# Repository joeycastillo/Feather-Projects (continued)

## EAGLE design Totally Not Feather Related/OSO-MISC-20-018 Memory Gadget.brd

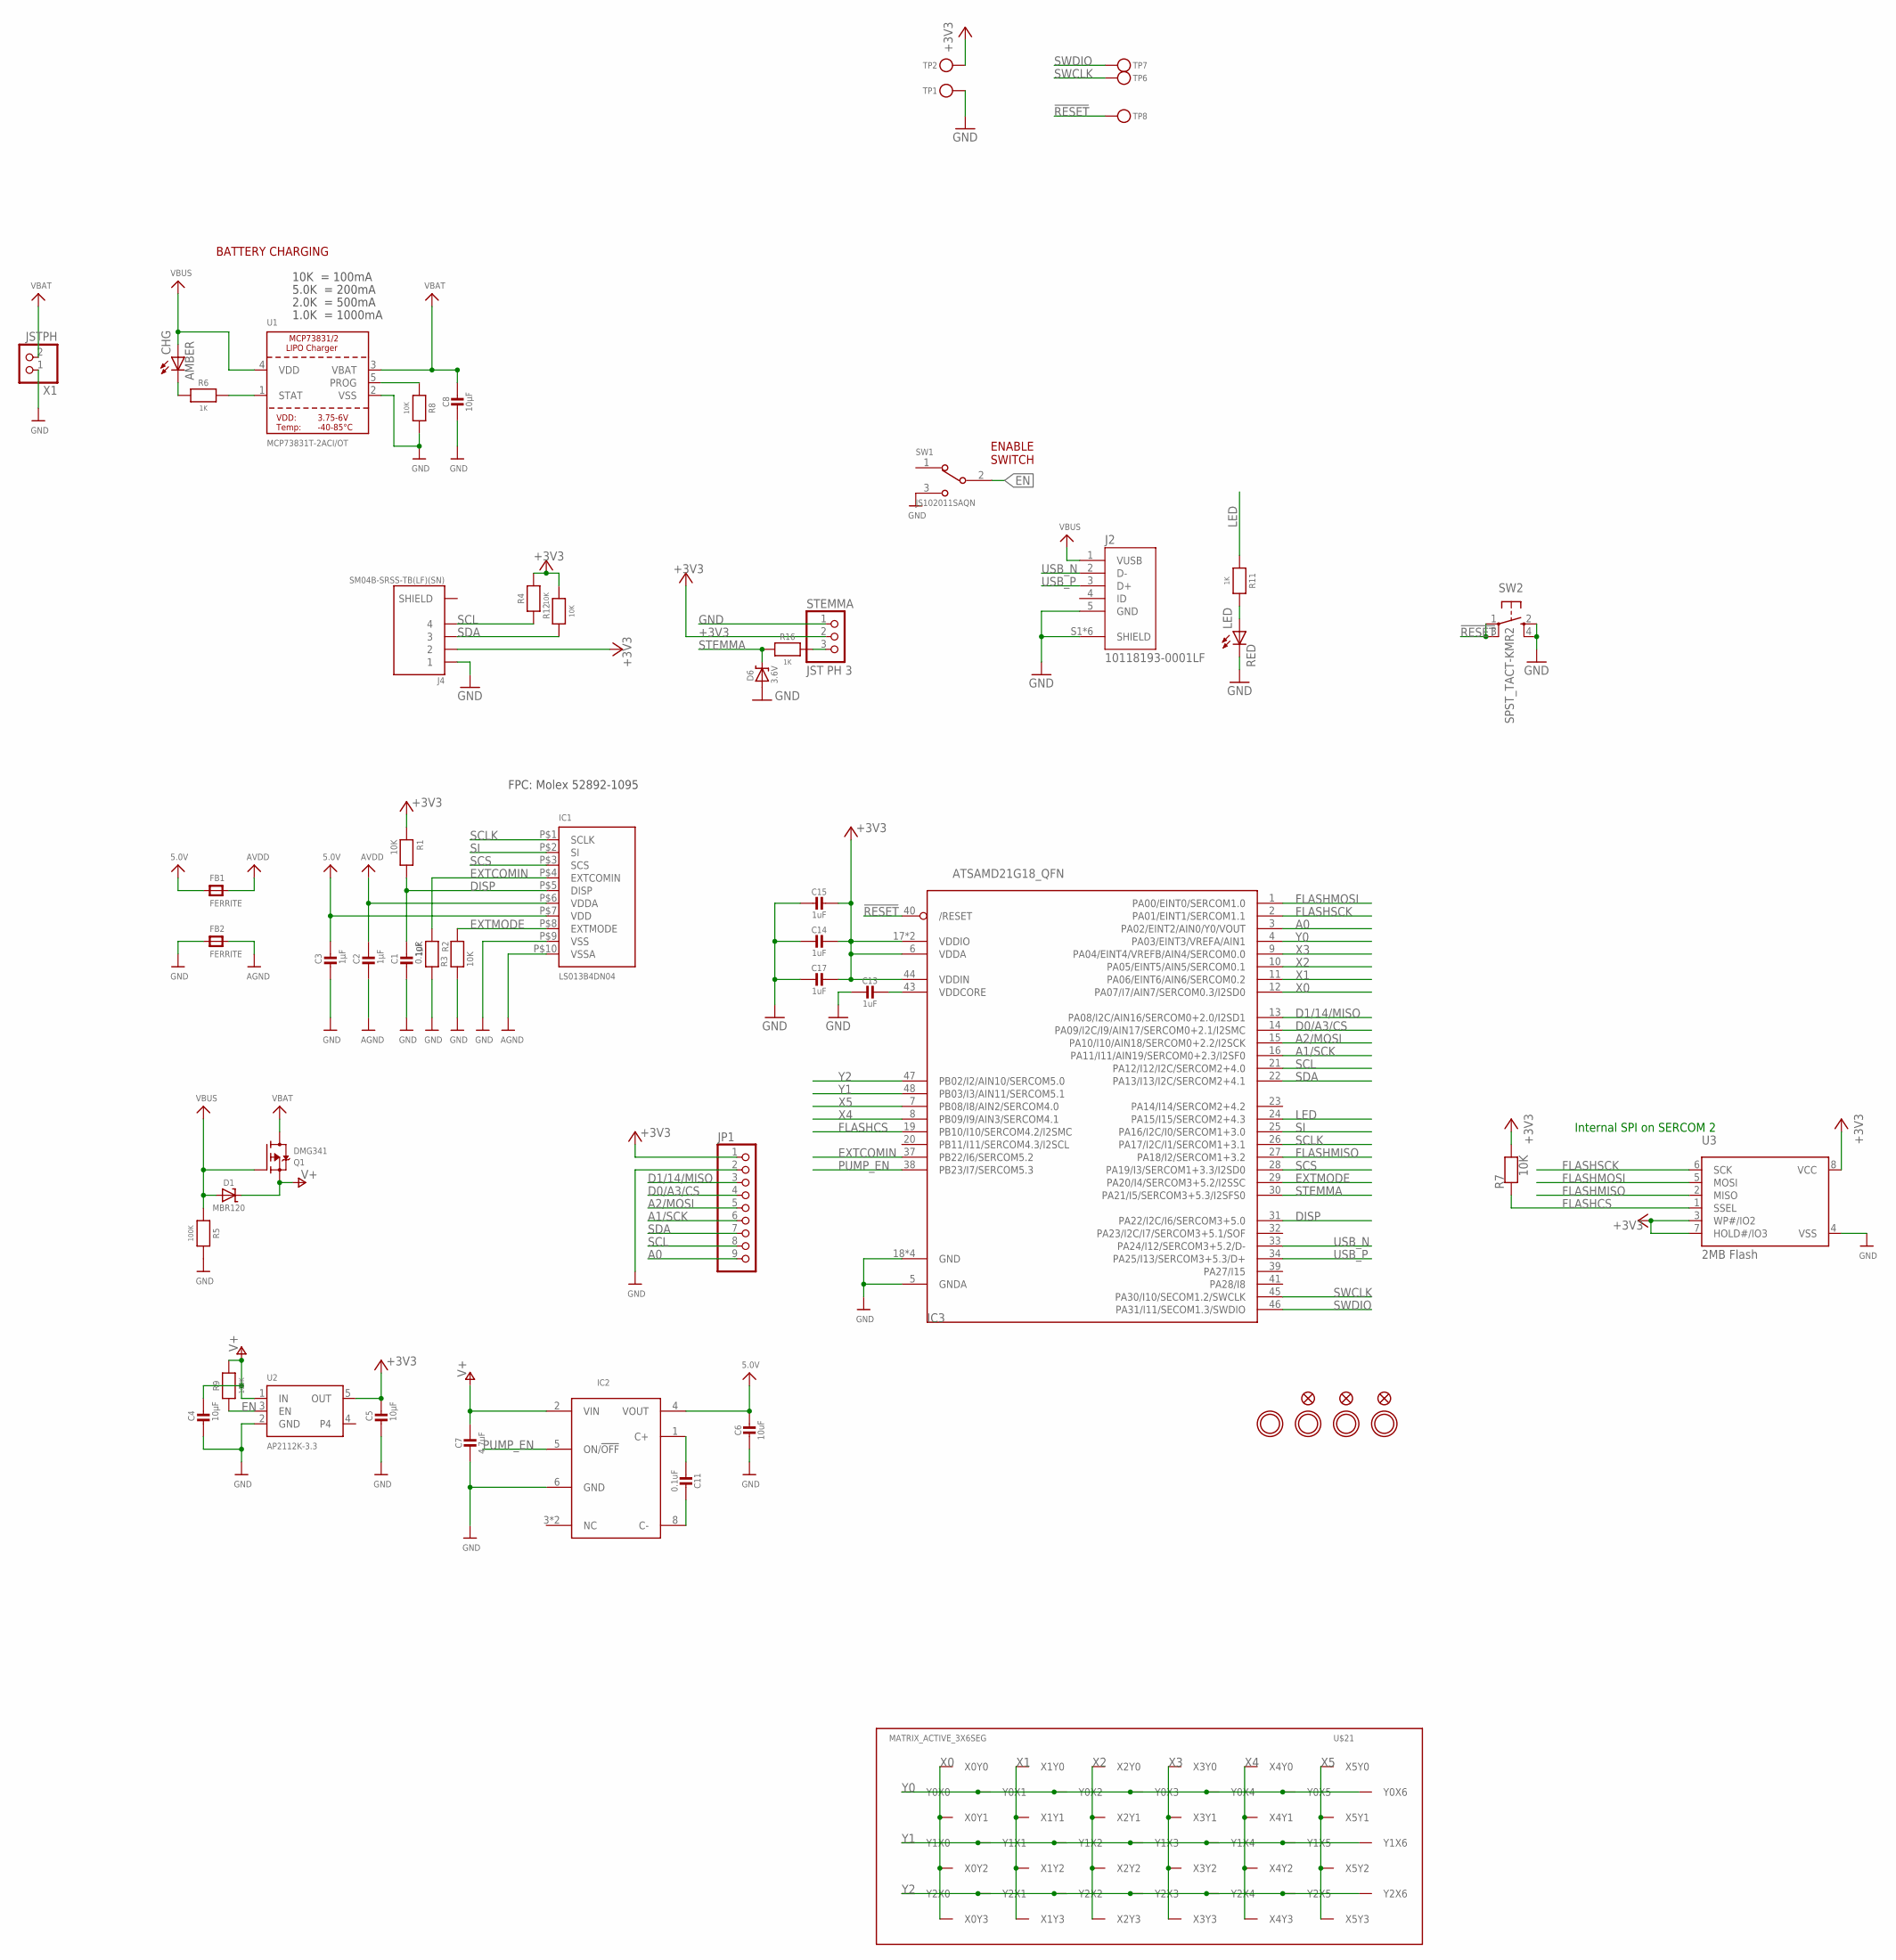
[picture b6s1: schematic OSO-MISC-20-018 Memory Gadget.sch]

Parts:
C1: 0.1µF; 0603-NO
C2: 1µF; 0805_10MGAP
C3: 1µF; 0805-NO
C4, C5, C8: 10µF; 0805-NO
C6: 10uF; 0805-NO
C7: 4.7uF; 0805-NO
C11: 0.1uF; 0805-NO
C13, C14, C15, C17: 1uF; 0603-NO
CHG: AMBER; CHIP-LED0805
D1: MBR120; SOD-123
D6: 3.6V; SOD-123
FB1, FB2: FERRITE; _0805
FID1, FID2, FID3: FIDUCIAL_1MM
IC1: LS013B4DN04; SHARP_2.7IN
IC2: S-882150APH; SNT-8A
IC3: ATSAMD21G18_QFN; TQFN48_7MM
J2: 10118193-0001LF; FCI_10118193-0001LF
J4: SM04B-SRSS-TB(LF)(SN); JST_SM04B-SRSS-TB(LF)(SN)
JP1: HEADER-1X9_JSTSH; JST_SH9
LED: RED; CHIP-LED0805
Q1: DMG341; SOT23-R
R1, R2, R3, R4, R7, R12: 10K; 0603-NO
R5, R9: 100K; 0805-NO
R6, R11: 1K; 0805-NO
R8: 10K; 0805-NO
R16: 1K; _0805MP
STEMMA: JST PH 3; JSTPH3
SW1: JS102011SAQN; SW_JS102011SAQN
SW2: SPST_TACT-KMR2; KMR2
TP1, TP2, TP6, TP7, TP8: TESTPOINTROUND2MMNO; TESTPOINT_ROUND_2MM_NO
U1: MCP73831T-2ACI/OT; SOT23-5
U2: AP2112K-3.3; SOT23-5
U3: 2MB Flash; SOIC8_150MIL
U$9, U$10, U$27, U$28: MOUNTINGHOLE2.5; MOUNTINGHOLE_2.5_PLATED
U$21: MATRIX_ACTIVE_3X6SEG; MATRIX_ACTIVE_3X6SEG_6MM
X1: JSTPH; JSTPH2

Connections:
5.0V: C3.1, C6.1, FB1.1, IC1.P$7 (VDD), IC2.4 (VOUT)
!RESET: IC3.40 (/RESET), SW2.1, SW2.3 (P1), TP8.P$1
+3V3: C5.1, C14.1, C15.1, C17.1, IC3.6 (VDDA), IC3.17 (VDDIO), IC3.36 (VDDIO), IC3.44 (VDDIN), J4.2, JP1.1, R1.1, R4.2, R7.2, R12.2, STEMMA.2, TP2.P$1, U2.5 (OUT), U3.3 (WP#/IO2), U3.7 (HOLD#/IO3), U3.8 (VCC)
A0: IC3.3 (PA02/EINT2/AIN0/Y0/VOUT), JP1.9
A1/SCK: IC3.16 (PA11/I11/AIN19/SERCOM0+2.3/I2SF0), JP1.6
A2/MOSI: IC3.15 (PA10/I10/AIN18/SERCOM0+2.2/I2SCK), JP1.5
AGND: C2.2, FB2.2, IC1.P$10 (VSSA)
AVDD: C2.1, FB1.2, IC1.P$6 (VDDA)
D0/A3/CS: IC3.14 (PA09/I2C/I9/AIN17/SERCOM0+2.1/I2SMC), JP1.4
D1/14/MISO: IC3.13 (PA08/I2C/AIN16/SERCOM0+2.0/I2SD1), JP1.3
DISP: C1.1, IC1.P$5 (DISP), IC3.31 (PA22/I2C/I6/SERCOM3+5.0), R1.2
EN: R9.1, SW1.2, U2.3 (EN)
EXTCOMIN: IC1.P$4 (EXTCOMIN), IC3.37 (PB22/I6/SERCOM5.2), R2.1
EXTMODE: IC1.P$8 (EXTMODE), IC3.29 (PA20/I4/SERCOM3+5.2/I2SSC), R3.2
FLASHCS: IC3.19 (PB10/I10/SERCOM4.2/I2SMC), R7.1, U3.1 (SSEL)
FLASHMISO: IC3.27 (PA18/I2/SERCOM1+3.2), U3.2 (MISO)
FLASHMOSI: IC3.1 (PA00/EINT0/SERCOM1.0), U3.5 (MOSI)
FLASHSCK: IC3.2 (PA01/EINT1/SERCOM1.1), U3.6 (SCK)
GND: C1.2, C3.2, C4.2, C5.2, C6.2, C7.2, C8.2, C13.2, C14.2, C15.2, C17.2, D6.A, FB2.1, IC1.P$9 (VSS), IC2.6 (GND), IC3.5 (GNDA), IC3.18 (GND), IC3.35 (GND), IC3.42 (GND), IC3.THERMAL (GND), J2.5 (GND), J2.S1 (SHIELD), J2.S2 (SHIELD), J2.S3 (SHIELD), J2.S4 (SHIELD), J2.S5 (SHIELD), J2.S6 (SHIELD), J4.1, JP1.2, LED.C, R2.2, R3.1, R5.2, R8.2, STEMMA.1, SW1.3, SW2.2 (S), SW2.4 (S1), TP1.P$1, U1.2 (VSS), U2.2 (GND), U3.4 (VSS), X1.1
LED: IC3.24 (PA15/I15/SERCOM2+4.3), R11.1
unnamed: LED.A, R11.2
unnamed: CHG.C, R6.1
unnamed: C11.2, IC2.1 (C+)
unnamed: C11.1, IC2.8 (C-)
PROG: R8.1, U1.5 (PROG)
PUMP_EN: IC2.5 (ON/!OFF), IC3.38 (PB23/I7/SERCOM5.3)
SCL: IC3.21 (PA12/I12/I2C/SERCOM2+4.0), J4.4, JP1.8, R4.1
SCLK: IC1.P$1 (SCLK), IC3.26 (PA17/I2C/I1/SERCOM1+3.1)
SCS: IC1.P$3 (SCS), IC3.28 (PA19/I3/SERCOM1+3.3/I2SD0)
SDA: IC3.22 (PA13/I13/I2C/SERCOM2+4.1), J4.3, JP1.7, R12.1
SI: IC1.P$2 (SI), IC3.25 (PA16/I2C/I0/SERCOM1+3.0)
STAT: R6.2, U1.1 (STAT)
STEMMA: D6.C, IC3.30 (PA21/I5/SERCOM3+5.3/I2SFS0), R16.2
STEMMA_: R16.1, STEMMA.3
SWCLK: IC3.45 (PA30/I10/SECOM1.2/SWCLK), TP6.P$1
SWDIO: IC3.46 (PA31/I11/SECOM1.3/SWDIO), TP7.P$1
USB_N: IC3.33 (PA24/I12/SERCOM3+5.2/D-), J2.2 (D-)
USB_P: IC3.34 (PA25/I13/SERCOM3+5.3/D+), J2.3 (D+)
V+: C4.1, C7.1, D1.C, IC2.2 (VIN), Q1.2 (S), R9.2, U2.1 (IN)
VBAT: C8.1, Q1.3 (D), U1.3 (VBAT), X1.2
VBUS: CHG.A, D1.A, J2.1 (VUSB), Q1.1 (G), R5.1, U1.4 (VDD)
VDDCORE: C13.1, IC3.43 (VDDCORE)
X0: IC3.12 (PA07/I7/AIN7/SERCOM0.3/I2SD0), U$21.X0Y0, U$21.X0Y1, U$21.X0Y2, U$21.X0Y3
X1: IC3.11 (PA06/EINT6/AIN6/SERCOM0.2), U$21.X1Y0, U$21.X1Y1, U$21.X1Y2, U$21.X1Y3
X2: IC3.10 (PA05/EINT5/AIN5/SERCOM0.1), U$21.X2Y0, U$21.X2Y1, U$21.X2Y2, U$21.X2Y3
X3: IC3.9 (PA04/EINT4/VREFB/AIN4/SERCOM0.0), U$21.X3Y0, U$21.X3Y1, U$21.X3Y2, U$21.X3Y3
X4: IC3.8 (PB09/I9/AIN3/SERCOM4.1), U$21.X4Y0, U$21.X4Y1, U$21.X4Y2, U$21.X4Y3
X5: IC3.7 (PB08/I8/AIN2/SERCOM4.0), U$21.X5Y0, U$21.X5Y1, U$21.X5Y2, U$21.X5Y3
Y0: IC3.4 (PA03/EINT3/VREFA/AIN1), U$21.Y0X0, U$21.Y0X1, U$21.Y0X2, U$21.Y0X3, U$21.Y0X4, U$21.Y0X5, U$21.Y0X6
Y1: IC3.48 (PB03/I3/AIN11/SERCOM5.1), U$21.Y1X0, U$21.Y1X1, U$21.Y1X2, U$21.Y1X3, U$21.Y1X4, U$21.Y1X5, U$21.Y1X6
Y2: IC3.47 (PB02/I2/AIN10/SERCOM5.0), U$21.Y2X0, U$21.Y2X1, U$21.Y2X2, U$21.Y2X3, U$21.Y2X4, U$21.Y2X5, U$21.Y2X6

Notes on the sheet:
FPC: Molex 52892-1095
ENABLE SWITCH
10K = 100mA
5.0K = 200mA
2.0K = 500mA
1.0K = 1000mA
BATTERY CHARGING
Internal SPI on SERCOM 2

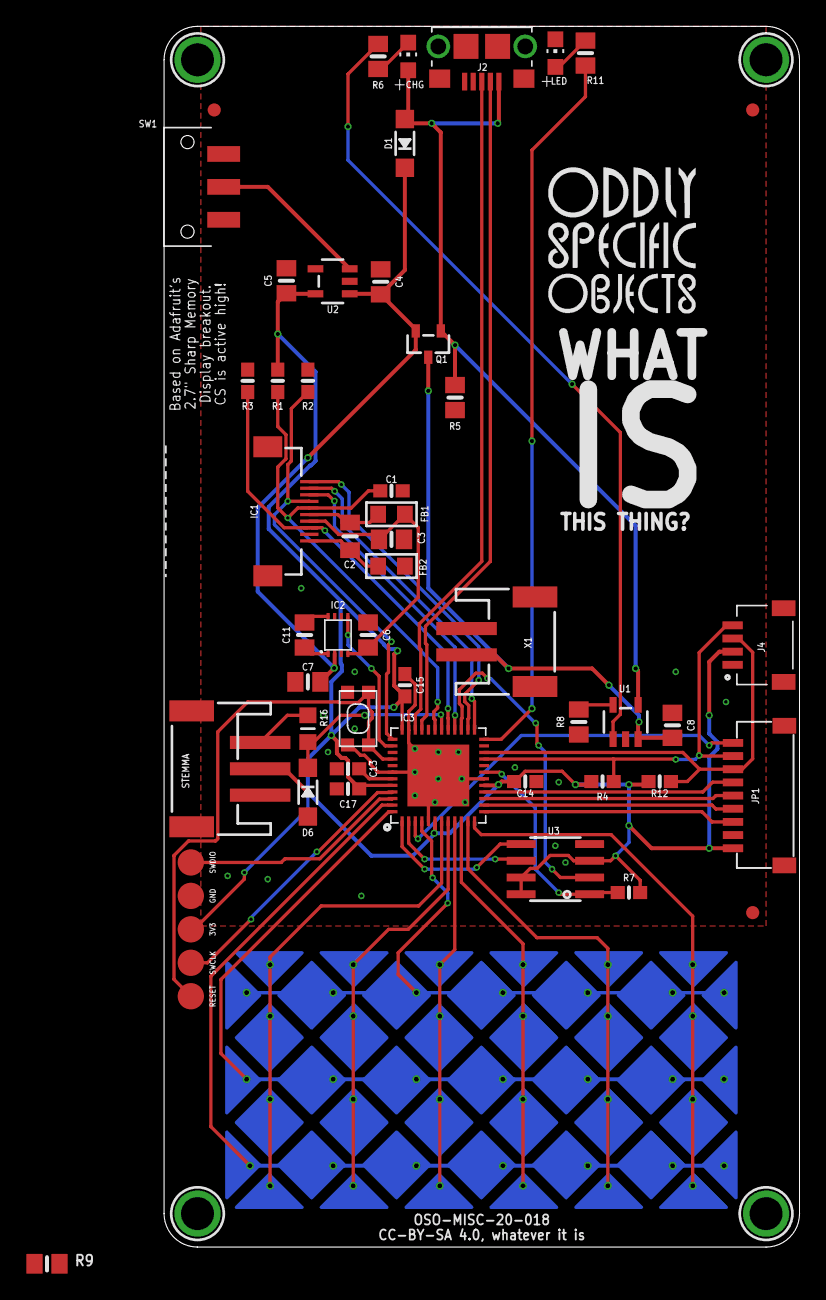
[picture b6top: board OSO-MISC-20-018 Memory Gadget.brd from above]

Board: 2 copper layers, 48.3 x 92.7 mm, 59 parts (1 on the bottom side), 51 nets.

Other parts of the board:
U$16: OSO_WORDMARK_THREELINE_450MIL_1000DPI

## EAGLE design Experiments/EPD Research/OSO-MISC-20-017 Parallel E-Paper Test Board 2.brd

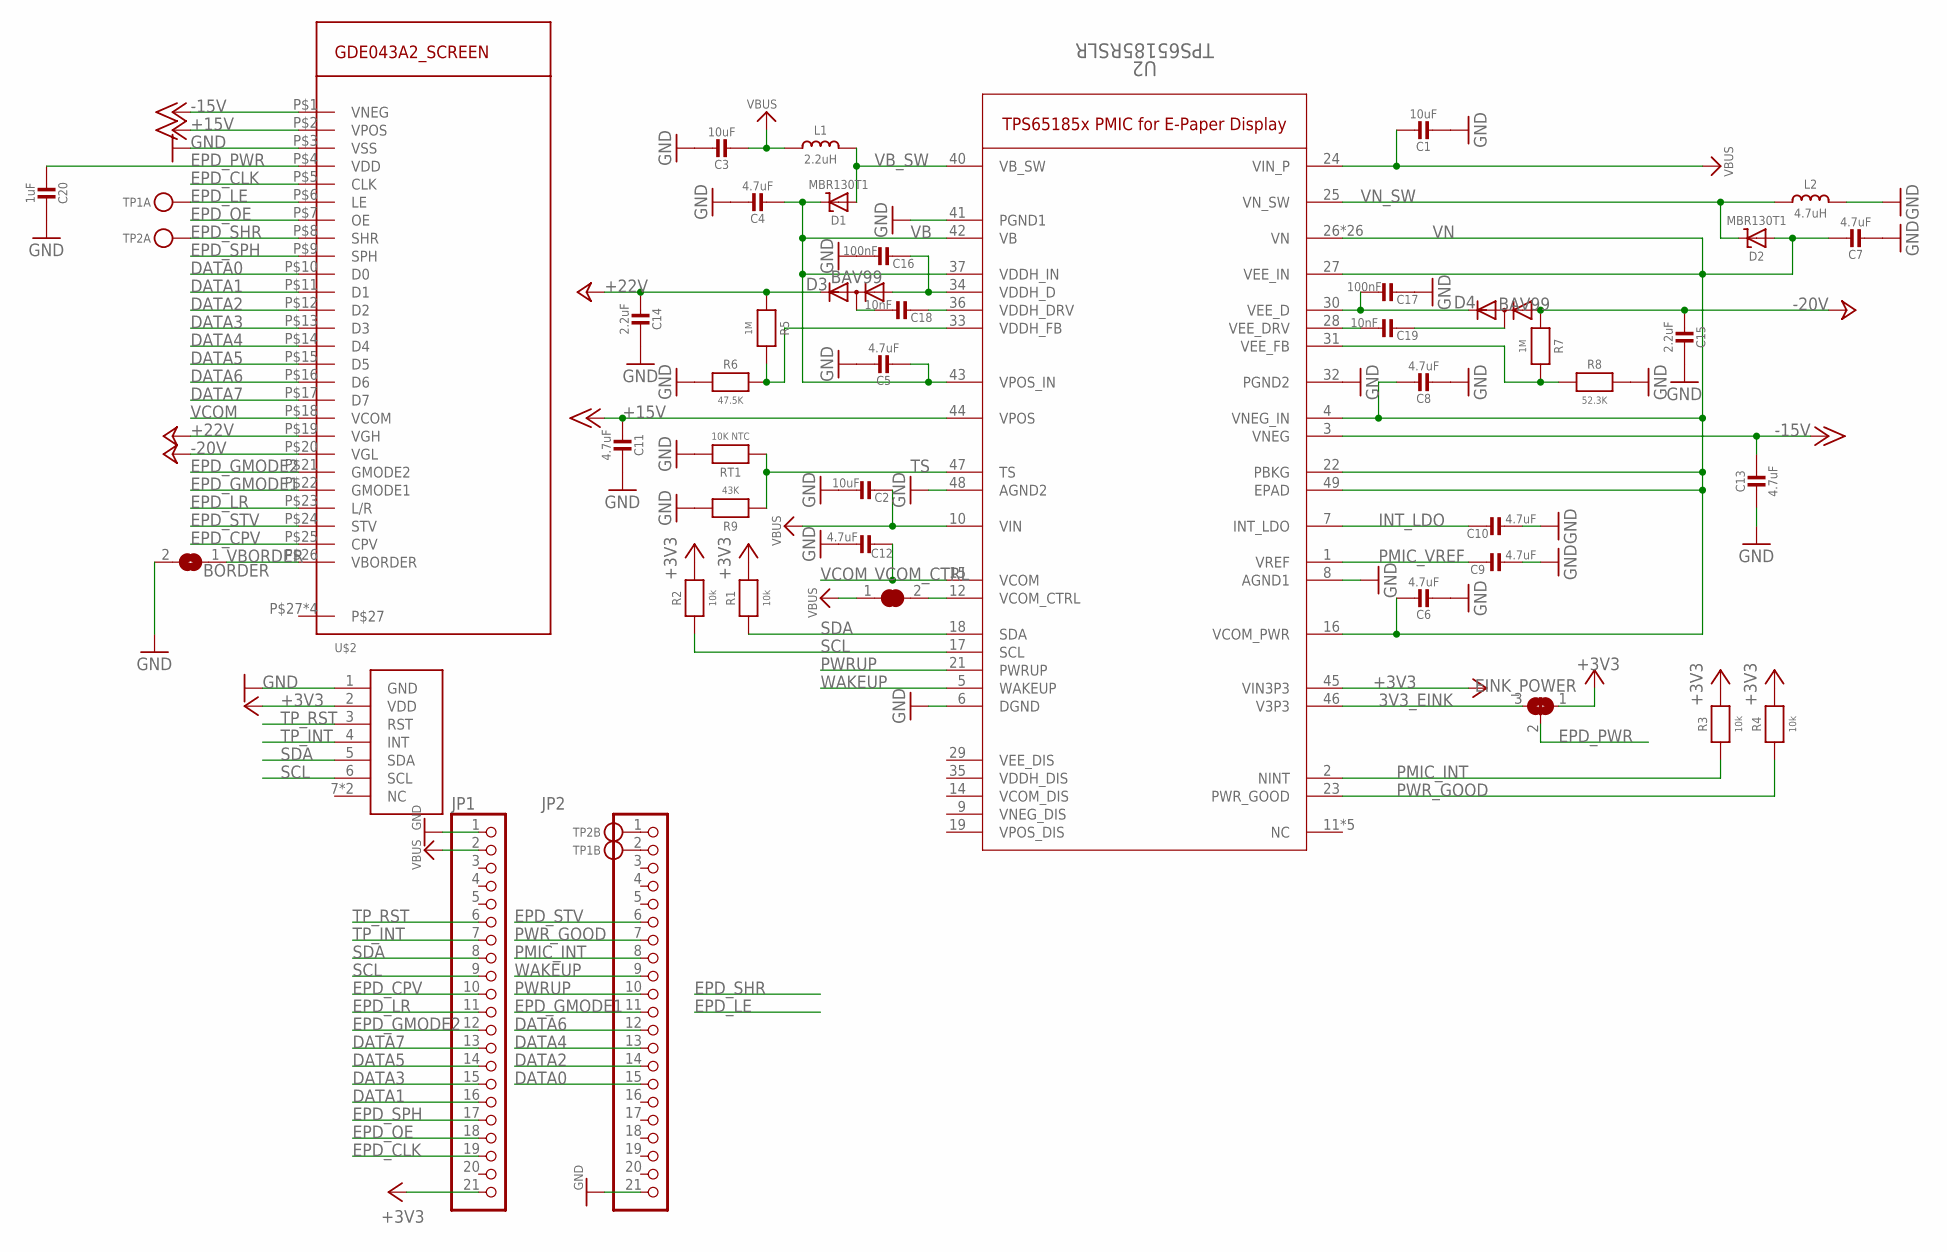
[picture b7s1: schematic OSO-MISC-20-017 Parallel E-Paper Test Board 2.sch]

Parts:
BORDER: SJ
C1, C2, C3: 10uF; 0805-NO
C4, C5, C6, C7, C8, C9, C10, C11, C12, C13: 4.7uF; 0805-NO
C14, C15: 2.2uF; 0805-NO
C16, C17: 100nF; 0805-NO
C18, C19: 10nF; 0805-NO
C20: 1uF; 0805-NO
D1, D2: MBR130T1; MICROBUILDER_SOD-123
D3, D4: BAV99; SOT23
EINK_POWER: SOLDERJUMPER_2WAY; SOLDERJUMPER_2WAY_OPEN_NOPASTE
JP1, JP2: PINHD-1X21; 1X21
L1: 2.2uH; MICROBUILDER_INDUCTOR_4X4MM_NR401_BIGPADS
L2: 4.7uH; MICROBUILDER_INDUCTOR_4X4MM_NR401_BIGPADS
R1, R2, R3, R4: 10k; 0805-NO
R5, R7: 1M; 0805-NO
R6: 47.5K; 0805-NO
R8: 52.3K; 0805-NO
R9: 43K; 0805-NO
RT1: 10K NTC; 0805-NO
TP1A, TP1B, TP2A, TP2B: TESTPOINT1.5X2.0MM_NOCREAM; PAD-1.5X2.0
U2: TPS65185RSLR; RSL48_4P4X4P4
U$2: GDE043A2_TP
U$3: GDE043A2_SCREEN; AXT526124
VCOM_CTRL: MICROBUILDER_SOLDERJUMPER_CLOSED; MICROBUILDER_SOLDERJUMPER_CLOSEDWIRE

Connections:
3V3_EINK: EINK_POWER.3, U2.46 (V3P3)
+3V3: EINK_POWER.1, JP1.21, R1.2, R2.2, R3.2, R4.2, U2.45 (VIN3P3), U$2.2 (VDD)
+15V: C11.2, U2.44 (VPOS), U$3.P$2 (VPOS)
+22V: C14.2, D3.2 (C), R5.1, U$3.P$19 (VGH)
-15V: C13.1, U2.3 (VNEG), U$3.P$1 (VNEG)
-20V: C15.2, D4.1 (A), R7.1, U$3.P$20 (VGL)
DATA0: JP2.15, U$3.P$10 (D0)
DATA1: JP1.16, U$3.P$11 (D1)
DATA2: JP2.14, U$3.P$12 (D2)
DATA3: JP1.15, U$3.P$13 (D3)
DATA4: JP2.13, U$3.P$14 (D4)
DATA5: JP1.14, U$3.P$15 (D5)
DATA6: JP2.12, U$3.P$16 (D6)
DATA7: JP1.13, U$3.P$17 (D7)
EPD_CLK: JP1.19, U$3.P$5 (CLK)
EPD_CPV: JP1.10, U$3.P$25 (CPV)
EPD_GMODE1: JP2.11, U$3.P$22 (GMODE1)
EPD_GMODE2: JP1.12, U$3.P$21 (GMODE2)
EPD_LE: TP1A.P$1, U$3.P$6 (LE)
EPD_LR: JP1.11, U$3.P$23 (L/R)
EPD_OE: JP1.18, U$3.P$7 (OE)
EPD_PWR: C20.2, EINK_POWER.2, U$3.P$4 (VDD)
EPD_SHR: TP2A.P$1, U$3.P$8 (SHR)
EPD_SPH: JP1.17, U$3.P$9 (SPH)
EPD_STV: JP2.6, U$3.P$24 (STV)
GND: BORDER.2, C1.1, C2.1, C3.1, C4.1, C5.1, C6.2, C7.2, C8.2, C9.2, C10.2, C11.1, C12.1, C13.2, C14.1, C15.1, C16.1, C17.2, C20.1, JP1.1, JP2.21, L2.P$2 (2), R6.1, R8.2, R9.2, RT1.2, U2.6 (DGND), U2.8 (AGND1), U2.32 (PGND2), U2.41 (PGND1), U2.48 (AGND2), U$2.1 (GND), U$3.P$3 (VSS)
INT_LDO: C10.1, U2.7 (INT_LDO)
unnamed: JP2.1, TP2B.P$1
unnamed: JP2.2, TP1B.P$1
unnamed: C18.1, D3.3 (AC)
unnamed: C19.2, D4.3 (AC)
PMIC_INT: JP2.8, R3.1, U2.2 (NINT)
PMIC_VREF: C9.1, U2.1 (VREF)
PWRUP: JP2.10, U2.21 (PWRUP)
PWR_GOOD: JP2.7, R4.1, U2.23 (PWR_GOOD)
SCL: JP1.9, R2.1, U2.17 (SCL), U$2.6 (SCL)
SDA: JP1.8, R1.1, U2.18 (SDA), U$2.5 (SDA)
TP_INT: JP1.7, U$2.4 (INT)
TP_RST: JP1.6, U$2.3 (RST)
TS: R9.1, RT1.1, U2.47 (TS)
VB: C4.2, C5.2, D1.C, U2.37 (VDDH_IN), U2.42 (VB), U2.43 (VPOS_IN)
VBORDER: BORDER.1, U$3.P$26 (VBORDER)
VBUS: C1.2, C2.2, C3.2, JP1.2, L1.P$1 (1), U2.10 (VIN), U2.24 (VIN_P), VCOM_CTRL.1
VB_SW: D1.A, L1.P$2 (2), U2.40 (VB_SW)
VCOM: C12.2, U2.15 (VCOM), U$3.P$18 (VCOM)
VCOM_CTRL: U2.12 (VCOM_CTRL), VCOM_CTRL.2
VDDH_D: C16.2, D3.1 (A), U2.34 (VDDH_D)
VDDH_DRV: C18.2, U2.36 (VDDH_DRV)
VDDH_FB: R5.2, R6.2, U2.33 (VDDH_FB)
VEE_D: C17.1, D4.2 (C), U2.30 (VEE_D)
VEE_DRV: C19.1, U2.28 (VEE_DRV)
VEE_FB: R7.2, R8.1, U2.31 (VEE_FB)
VN: C6.1, C7.1, C8.1, D2.A, U2.4 (VNEG_IN), U2.16 (VCOM_PWR), U2.22 (PBKG), U2.26 (VN), U2.27 (VEE_IN), U2.49 (EPAD), U2.P$1 (VN), U2.P$2 (VN), U2.P$3 (VN), U2.P$4 (VN), U2.P$5 (VN), U2.P$6 (VN), U2.P$7 (VN), U2.P$8 (VN), U2.P$9 (VN), U2.P$10 (VN), U2.P$11 (VN), U2.P$12 (VN), U2.P$13 (VN), U2.P$14 (VN), U2.P$15 (VN), U2.P$16 (VN), U2.P$17 (VN), U2.P$18 (VN), U2.P$19 (VN), U2.P$20 (VN), U2.P$21 (VN), U2.P$22 (VN), U2.P$23 (VN), U2.P$24 (VN), U2.P$25 (VN)
VN_SW: D2.C, L2.P$1 (1), U2.25 (VN_SW)
WAKEUP: JP2.9, U2.5 (WAKEUP)

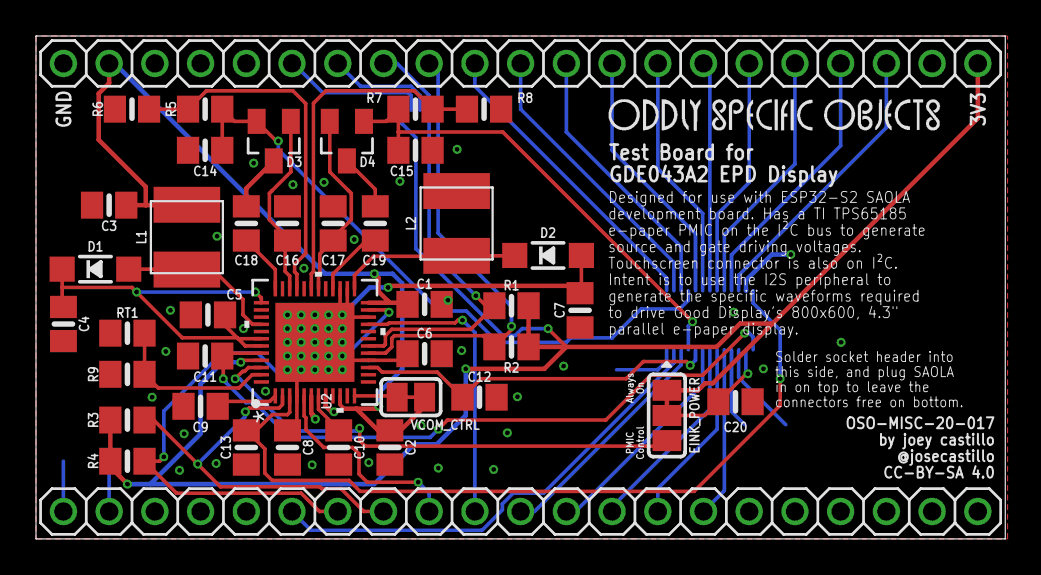
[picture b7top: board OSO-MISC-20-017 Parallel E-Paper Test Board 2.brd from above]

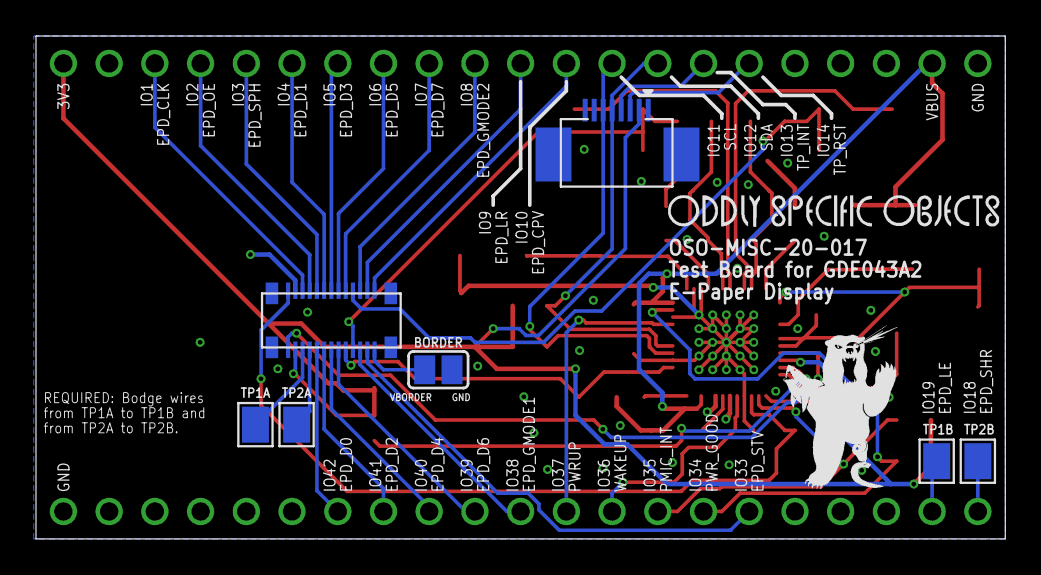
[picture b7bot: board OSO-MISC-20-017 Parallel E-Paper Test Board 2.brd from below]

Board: 2 copper layers, 53.8 x 27.9 mm, 51 parts (9 on the bottom side), 55 nets.

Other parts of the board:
U$4: OSO_BEAR_250X360MIL_1000DPI
U$10, U$11: OSO_WORDMARK_ONELINE_725MIL_1000DPI

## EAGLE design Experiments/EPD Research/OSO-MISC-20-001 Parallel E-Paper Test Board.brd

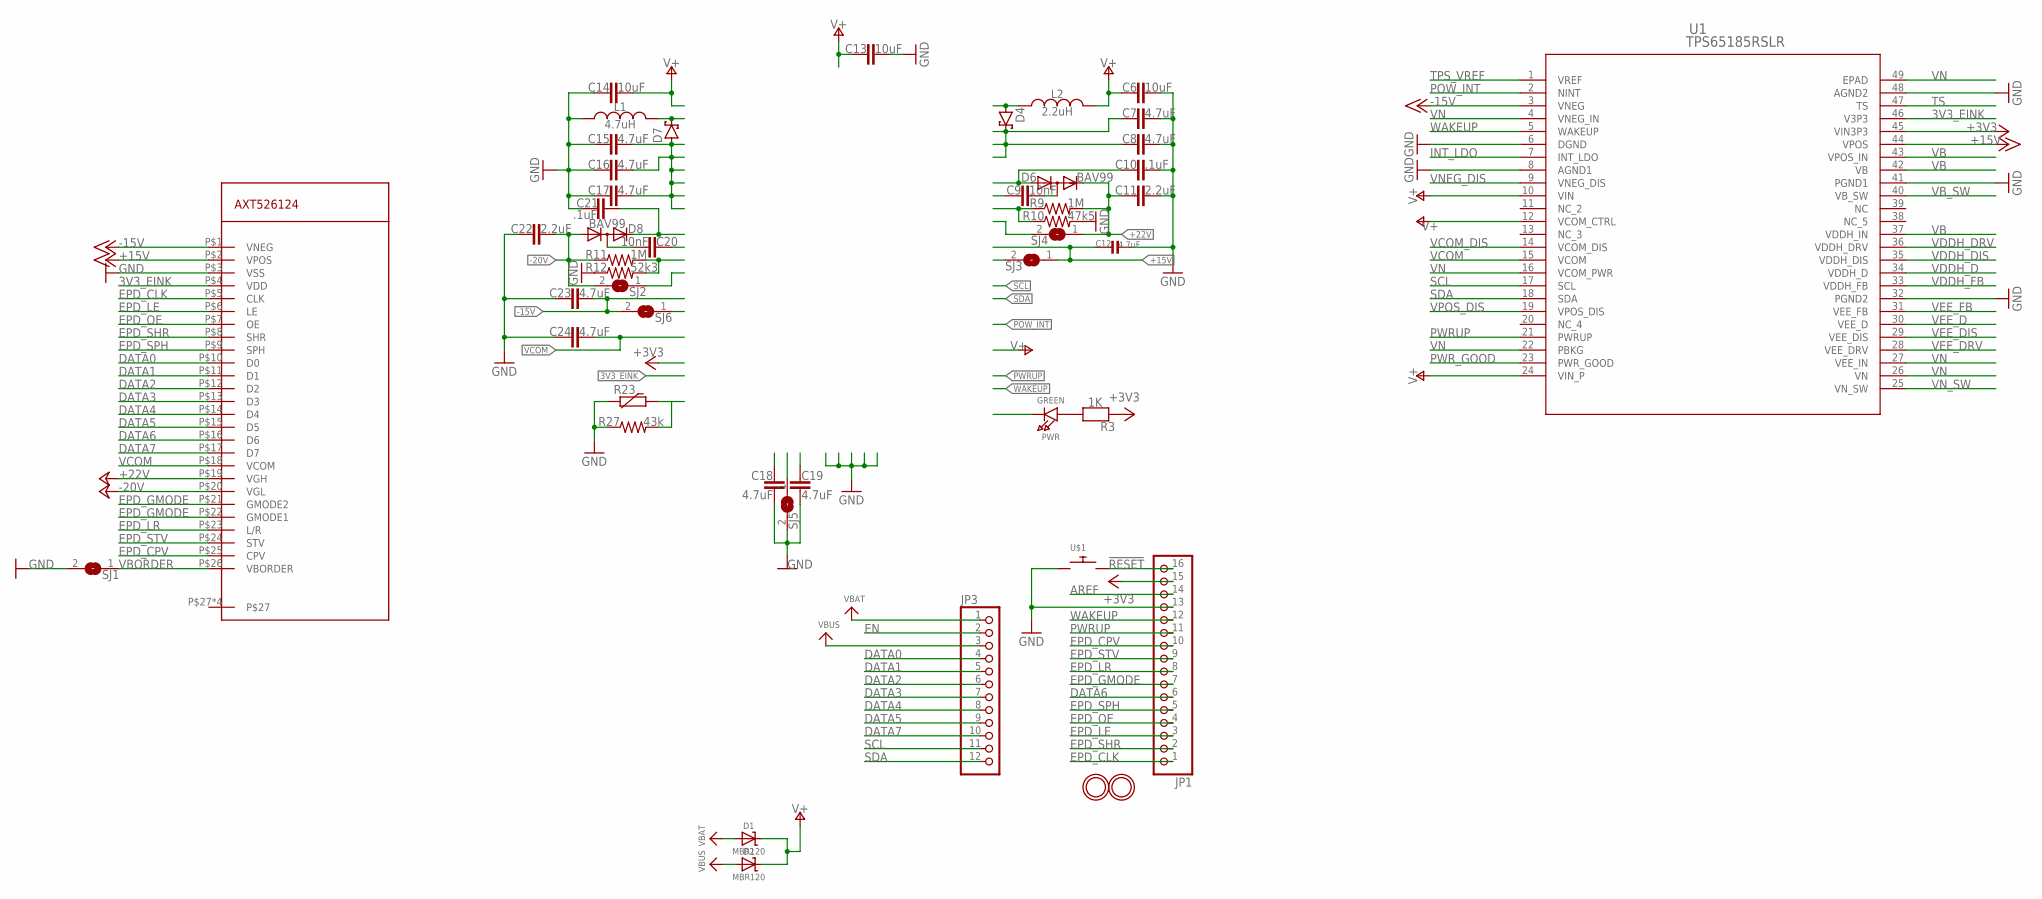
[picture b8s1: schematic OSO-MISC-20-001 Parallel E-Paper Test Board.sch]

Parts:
C6, C13, C14: 10uF; C0805K
C7, C8, C15, C16, C17, C18, C19, C23, C24: 4.7uF; C0805K
C9, C20: 10nF; C0805K
C10, C21: .1uF; C0805K
C11, C22: 2.2uF; C0805K
C12: 4.7uF; 0805_10MGAP
D1, D2: MBR120; SOD-123
D4, D7: MBR130T3G; SOD123
D6, D8: BAV99; SOT23
JP1: HEADER-1X16_MIN; 1X16_ROUND_MIN
JP3: HEADER-1X12_MIN; 1X12_ROUND_MIN
L1: 4.7uH; NR4012
L2: 2.2uH; NR4012
PWR: GREEN; CHIPLED_0805_NOOUTLINE
R3: 1K; 0805-NO
R9, R11: 1M; R0805
R10: 47k5; R0805
R12: 52k3; R0805
R23: R-EU_R0805; R0805
R27: 43k; R0805
SJ1, SJ2, SJ3, SJ4, SJ5, SJ6: SJ
U1: TPS65185RSLR; RSL48_4P4X4P4
U$1: SPST_TACTILE_SWITCHTHRU-SECONDTRY; MJTP1250-TRY2
U$2: AXT526124
U$31, U$32: MOUNTINGHOLE2.5; MOUNTINGHOLE_2.5_PLATED

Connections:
3V3_EINK: U1.46 (V3P3), U$2.P$4 (VDD)
!RESET: JP1.16, U$1.P$2
+3V3: JP1.15, R3.1, U1.45 (VIN3P3)
+15V: C12.2, SJ3.1, U1.44 (VPOS), U$2.P$2 (VPOS)
+22V: C11.1, D6.2 (C), R9.2, SJ4.1, U$2.P$19 (VGH)
-15V: C23.2, SJ6.2, U1.3 (VNEG), U$2.P$1 (VNEG)
-20V: C22.2, D8.1 (A), R11.1, SJ2.2, U$2.P$20 (VGL)
AREF: JP1.14
DATA0: JP3.4, U$2.P$10 (D0)
DATA1: JP3.5, U$2.P$11 (D1)
DATA2: JP3.6, U$2.P$12 (D2)
DATA3: JP3.7, U$2.P$13 (D3)
DATA4: JP3.8, U$2.P$14 (D4)
DATA5: JP3.9, U$2.P$15 (D5)
DATA6: JP1.6, U$2.P$16 (D6)
DATA7: JP3.10, U$2.P$17 (D7)
EN: JP3.2
EPD_CLK: JP1.1, U$2.P$5 (CLK)
EPD_CPV: JP1.10, U$2.P$25 (CPV)
EPD_GMODE: JP1.7, U$2.P$21 (GMODE2), U$2.P$22 (GMODE1)
EPD_LE: JP1.3, U$2.P$6 (LE)
EPD_LR: JP1.8, U$2.P$23 (L/R)
EPD_OE: JP1.4, U$2.P$7 (OE)
EPD_SHR: JP1.2, U$2.P$8 (SHR)
EPD_SPH: JP1.5, U$2.P$9 (SPH)
EPD_STV: JP1.9, U$2.P$24 (STV)
GND: C6.2, C7.2, C8.2, C10.2, C11.2, C12.1, C13.2, C14.1, C15.1, C16.1, C17.1, C18.1, C19.1, C21.1, C22.1, C23.1, C24.1, JP1.13, L1.P$1, R10.2, R12.1, R23.1, R27.1, SJ1.2, SJ5.2, U1.6 (DGND), U1.8 (AGND1), U1.32 (PGND2), U1.41 (PGND1), U1.48 (AGND2), U$1.P$1, U$2.P$3 (VSS)
INT_LDO: C18.2, U1.7 (INT_LDO)
unnamed: PWR.A, R3.2
unnamed: C9.2, D6.3 (AC)
unnamed: C20.2, D8.3 (AC)
POW_INT: U1.2 (NINT)
PWRUP: JP1.11, U1.21 (PWRUP)
PWR_GOOD: PWR.C, U1.23 (PWR_GOOD)
SCL: JP3.11, U1.17 (SCL)
SDA: JP3.12, U1.18 (SDA)
TPS_VREF: C19.2, U1.1 (VREF)
TS: R23.2, R27.2, U1.47 (TS)
V+: C6.1, C13.1, C14.2, D1.C, D2.C, L2.P$2, U1.10 (VIN), U1.12 (VCOM_CTRL), U1.24 (VIN_P)
VB: C7.1, C8.1, D4.1 (C), U1.37 (VDDH_IN), U1.42 (VB), U1.43 (VPOS_IN)
VBAT: D1.A, JP3.1
VBORDER: SJ1.1, U$2.P$26 (VBORDER)
VBUS: D2.A, JP3.3
VB_SW: D4.2 (A), L2.P$1, U1.40 (VB_SW)
VCOM: C24.2, U1.15 (VCOM), U$2.P$18 (VCOM)
VCOM_DIS: SJ5.1, U1.14 (VCOM_DIS)
VDDH_D: C10.1, D6.1 (A), U1.34 (VDDH_D)
VDDH_DIS: SJ4.2, U1.35 (VDDH_DIS)
VDDH_DRV: C9.1, U1.36 (VDDH_DRV)
VDDH_FB: R9.1, R10.1, U1.33 (VDDH_FB)
VEE_D: C21.2, D8.2 (C), U1.30 (VEE_D)
VEE_DIS: SJ2.1, U1.29 (VEE_DIS)
VEE_DRV: C20.1, U1.28 (VEE_DRV)
VEE_FB: R11.2, R12.2, U1.31 (VEE_FB)
VN: C15.2, C16.2, C17.2, D7.2 (A), U1.4 (VNEG_IN), U1.16 (VCOM_PWR), U1.22 (PBKG), U1.26 (VN), U1.27 (VEE_IN), U1.49 (EPAD)
VNEG_DIS: SJ6.1, U1.9 (VNEG_DIS)
VN_SW: D7.1 (C), L1.P$2, U1.25 (VN_SW)
VPOS_DIS: SJ3.2, U1.19 (VPOS_DIS)
WAKEUP: JP1.12, U1.5 (WAKEUP)

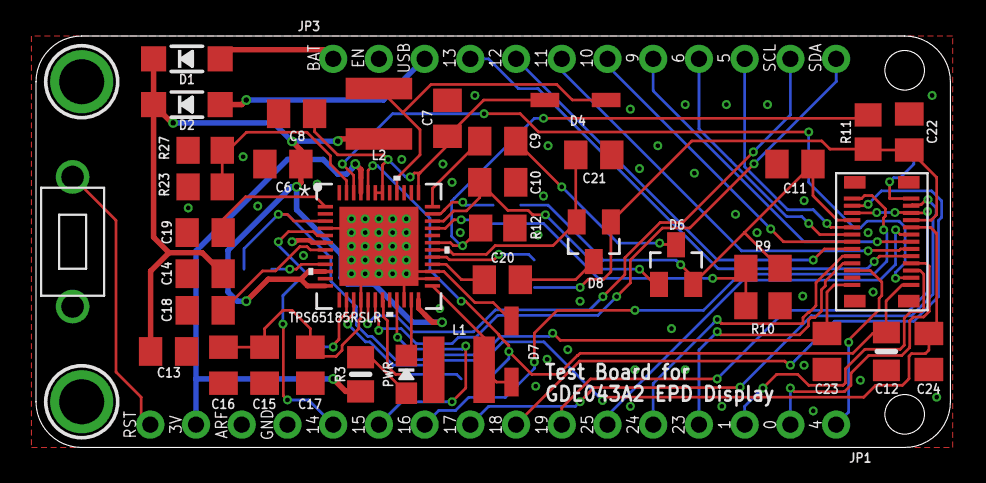
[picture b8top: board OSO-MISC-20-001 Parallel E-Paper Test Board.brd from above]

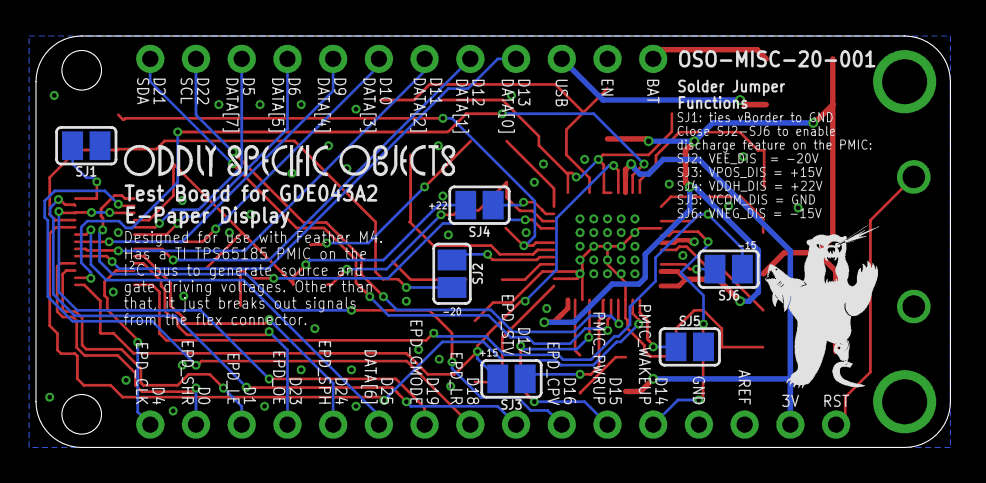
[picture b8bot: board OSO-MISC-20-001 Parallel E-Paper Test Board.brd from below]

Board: 2 copper layers, 50.8 x 22.9 mm, 50 parts (8 on the bottom side), 56 nets.

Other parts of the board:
U$4: OSO_WORDMARK_ONELINE_725MIL_1000DPI
U$7: OSO_BEAR_250X360MIL_1000DPI

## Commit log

2019-08-09 rearranging files
2019-08-13 readme about eBook wing
2019-09-07 WIP simple feather for future concepts
2019-09-08 first rev of the hand-solderable one, WIP the QFN package
2019-09-08 tweak some silkscreen text
2019-09-20 babel wing rev A as submitted to OSH Park
2019-10-23 silkscreen tweaks
2019-10-23 swap miso and sck to match intended muxing
2019-11-09 final version of SAMD11 24QFN Feather as submitted to OSH Park
2019-11-10 unswap swdio and swclk pins
2019-11-10 protoboard wing A1 rev 01
2019-11-10 protoboard wing B1 rev 01
2019-11-12 add revision label
2019-11-17 fix SPI pin muxing
2019-12-26 capacitive touch experiments
2019-12-26 fix swdio/swclk mixup
2019-12-26 add cap touch readme
2019-12-26 add images
2020-01-13 through hole SAMD11 board
2020-01-18 january projects
2020-01-18 update image to reflect board as made
2020-01-24 cap touch matrix featherwing
2020-03-29 add bpm bike light
2020-03-30 add SAML21 feather (never finished)
2020-03-30 add mostly through hole SAMD11 Feather
2020-03-30 add cap touch experiments from january
2020-03-31 scoot usb breakout up a bit
2020-04-19 add temperatrure hat
2020-04-21 new round of sensor boards
2020-04-21 add SAMD51 sensor cap mainboard
2020-04-21 add SAMD11 sensor cap mainboard
2020-04-22 update SAMD11 feathers
2020-04-29 add led resistor values
2020-04-29 add part numbers
2020-06-05 simple samd11 feather a1 rev 04
2020-08-14 alphanumeric display module
2020-08-21 add BOM and assembly csv for segment module
2020-08-21 add trinket swd board
2020-11-23 rename old featherwing experiment
2020-12-01 new stuff
2020-12-11 add EN pull-up, fix SPI flash pin selection
2020-12-11 update trinket SWD adapter
2020-12-27 add PyRadio experiment
2021-03-06 low power lcd feather
2021-03-17 saml22 feather: rename segment pins for clarity
2021-03-17 saml22 feather: add WIP bezel
2022-02-04 ring thing
2022-03-05 LCD wing
